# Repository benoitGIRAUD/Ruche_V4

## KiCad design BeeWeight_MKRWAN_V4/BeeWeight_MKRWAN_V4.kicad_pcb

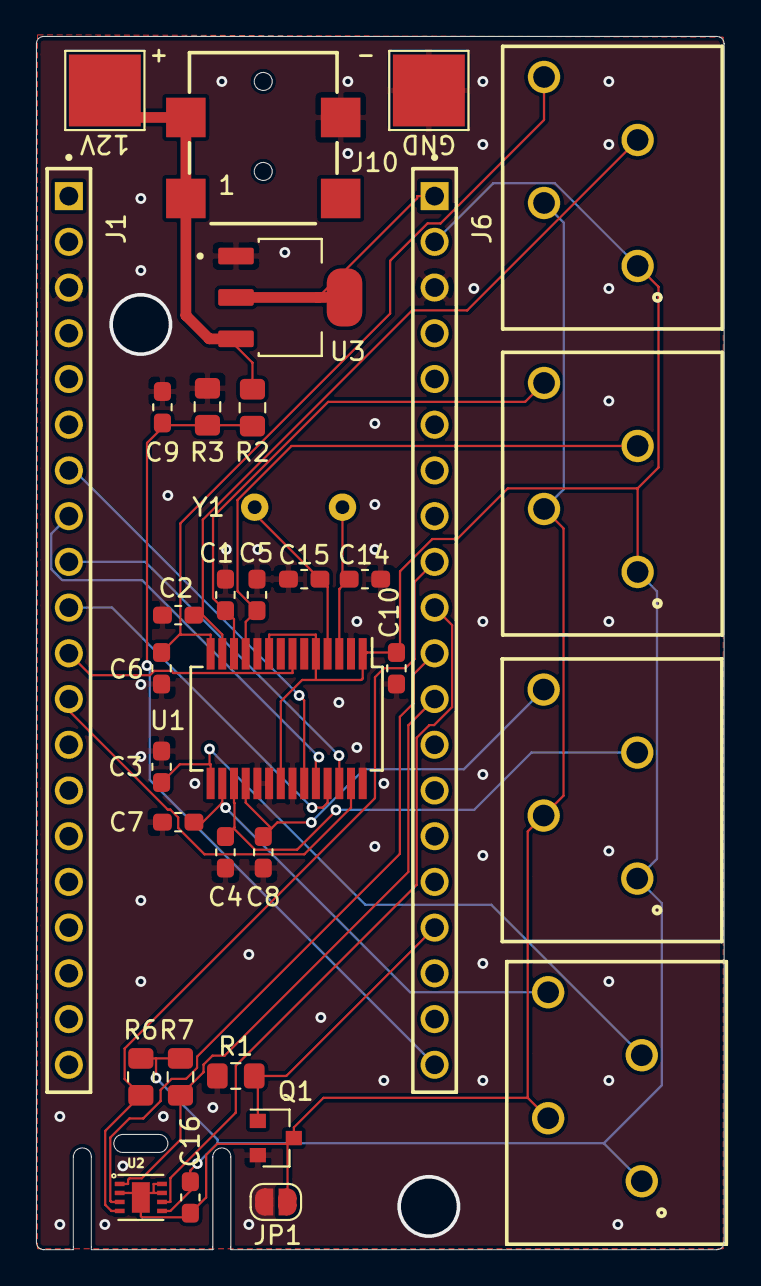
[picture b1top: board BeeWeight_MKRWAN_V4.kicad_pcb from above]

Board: 4 copper layers, 38.2 x 67.4 mm, 33 parts (0 on the bottom side), 27 nets.

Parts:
12V: TestPoint; TestPoint_Pad_4.0x4.0mm
C1, C2, C3, C4, C5, C6, C7, C8: 10nF; C_0603_1608Metric_Pad1.05x0.95mm_HandSolder
C9, C10, C16: 100nF; C_0603_1608Metric_Pad1.05x0.95mm_HandSolder
C14, C15: 18pF; C_0603_1608Metric_Pad1.05x0.95mm_HandSolder
GND: TestPoint; TestPoint_Pad_4.0x4.0mm
J1, J6: SSW-120-01-X-S; SAMTEC_SSW-120-01-X-S
J2, J3, J4, J5: 691412120004B; TermBlock_1x04_P3.50mm Wurth_691412120004B
J10: 694103107102
JP1: SolderJumper_2_Open; SolderJumper-2_P1.3mm_Open_RoundedPad1.0x1.5mm
Q1: IRLML6244; SOT-23
R1: 1M; R_0805_2012Metric_Pad1.15x1.40mm_HandSolder
R2: 560k; R_0805_2012Metric_Pad1.15x1.40mm_HandSolder
R3: 100k; R_0805_2012Metric_Pad1.15x1.40mm_HandSolder
R6, R7: 10K; R_0805_2012Metric_Pad1.15x1.40mm_HandSolder
U1: ADS1241
U2: SHT30-DIS-B; DFN250X250X100-9N
U3: LDL1117S50R; SOT230P700X180-4N
Y1: Crystal; Crystal-4Mhz-TH-Wurth-830027298B

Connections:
/3V3: C10.2, C16.1, J2.1, J3.1, J4.1, J5.1, J6.02, R6.2, R7.2, U1.1, U1.5, U1.9, U1.21, U2.5
/12V: 12V.1, J10.1, J10.A1, R2.2, U3.3
/AIN0: C5.1, J5.3, U1.11
/AIN1: C1.1, J5.4, U1.12
/AIN2: C4.1, J4.3, U1.17
/AIN3: C8.1, J4.4, U1.18
/AIN4: C2.1, J2.3, U1.13
/AIN5: C6.1, J2.4, U1.14
/AIN6: C3.1, J3.3, U1.15
/AIN7: C7.1, J3.4, U1.16
/GND_LowPower: C16.2, J2.2, J3.2, J4.2, J5.2, JP1.1, Q1.3, U2.2, U2.7, U2.8, U2.9
/IO4_VBAT_12V: C9.1, J6.20, R2.1, R3.2
/IO7_CMD_MOS: J6.17, Q1.1, R1.2
/IO17_SDA: J6.12, R7.1, U2.1
/IO18_SCL: J6.09, R6.1, U2.4
/IO19_SHT_ALERT: J6.11, U2.3
/IO21_SHT_RST: J6.10, U2.6
/IO34_CS: J1.07, U1.23
/IO35_MOSI: J1.08, U1.24
/IO36_SCLK: J1.09, U1.26
/IO37_MISO: J1.10, U1.25
/IO38_PDWN: J1.11, U1.7
/IO39_DRDY: J1.12, U1.27
/VDD_5V: J6.01, U3.2, U3.4
GND: C1.2, C2.2, C3.2, C4.2, C5.2, C6.2, C7.2, C8.2, C9.2, C10.1, C14.1, C15.2, GND.1, J1.03, J6.03, J10.2, JP1.2, Q1.2, R1.1, R3.1, U1.2, U1.10, U1.19, U1.20, U1.22, U1.28, U3.1
unnamed: C14.2, U1.3, Y1.1
unnamed: C15.1, U1.4, Y1.2

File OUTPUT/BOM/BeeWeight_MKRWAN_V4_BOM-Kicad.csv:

"Id";"Référence";"Boîtier";"Quantité";"Désignation";"Fournisseur et réf";
1;"U1";"ADS1241";1;"ADS1241";;;
2;"JP1";"SolderJumper-2_P1.3mm_Open_RoundedPad1.0x1.5mm";1;"SolderJumper_2_Open";;;
3;"Y1";"Crystal-4Mhz-TH-Wurth-830027298B";1;"Crystal";;;
4;"J3,J5,J4,J2";"TermBlock_1x04_P3.50mm Wurth_691412120004B";4;"691412120004B";;;
5;"C7,C1,C2,C3,C4,C5,C6,C8";"C_0603_1608Metric_Pad1.05x0.95mm_HandSolder";8;"10nF";;;
6;"C9,C10,C16";"C_0603_1608Metric_Pad1.05x0.95mm_HandSolder";3;"100nF";;;
7;"C14,C15";"C_0603_1608Metric_Pad1.05x0.95mm_HandSolder";2;"18pF";;;
8;"Q1";"SOT-23";1;"IRLML6244";;;
9;"R1";"R_0805_2012Metric_Pad1.15x1.40mm_HandSolder";1;"1M";;;
10;"R2";"R_0805_2012Metric_Pad1.15x1.40mm_HandSolder";1;"560k";;;
11;"R3";"R_0805_2012Metric_Pad1.15x1.40mm_HandSolder";1;"100k";;;
12;"R6,R7";"R_0805_2012Metric_Pad1.15x1.40mm_HandSolder";2;"10K";;;
13;"U2";"DFN250X250X100-9N";1;"SHT30-DIS-B";;;
14;"J10";"694103107102";1;"694103107102";;;
15;"J1";"SAMTEC_SSW-120-01-X-S";1;"SSW-120-01-X-S";;;
16;"J6";"SAMTEC_SSW-120-01-X-S";1;"SSW-120-01-X-S";;;
17;"U3";"SOT230P700X180-4N";1;"LDL1117S50R";;;
18;"GND,12V";"TestPoint_Pad_4.0x4.0mm";2;"TestPoint";;;

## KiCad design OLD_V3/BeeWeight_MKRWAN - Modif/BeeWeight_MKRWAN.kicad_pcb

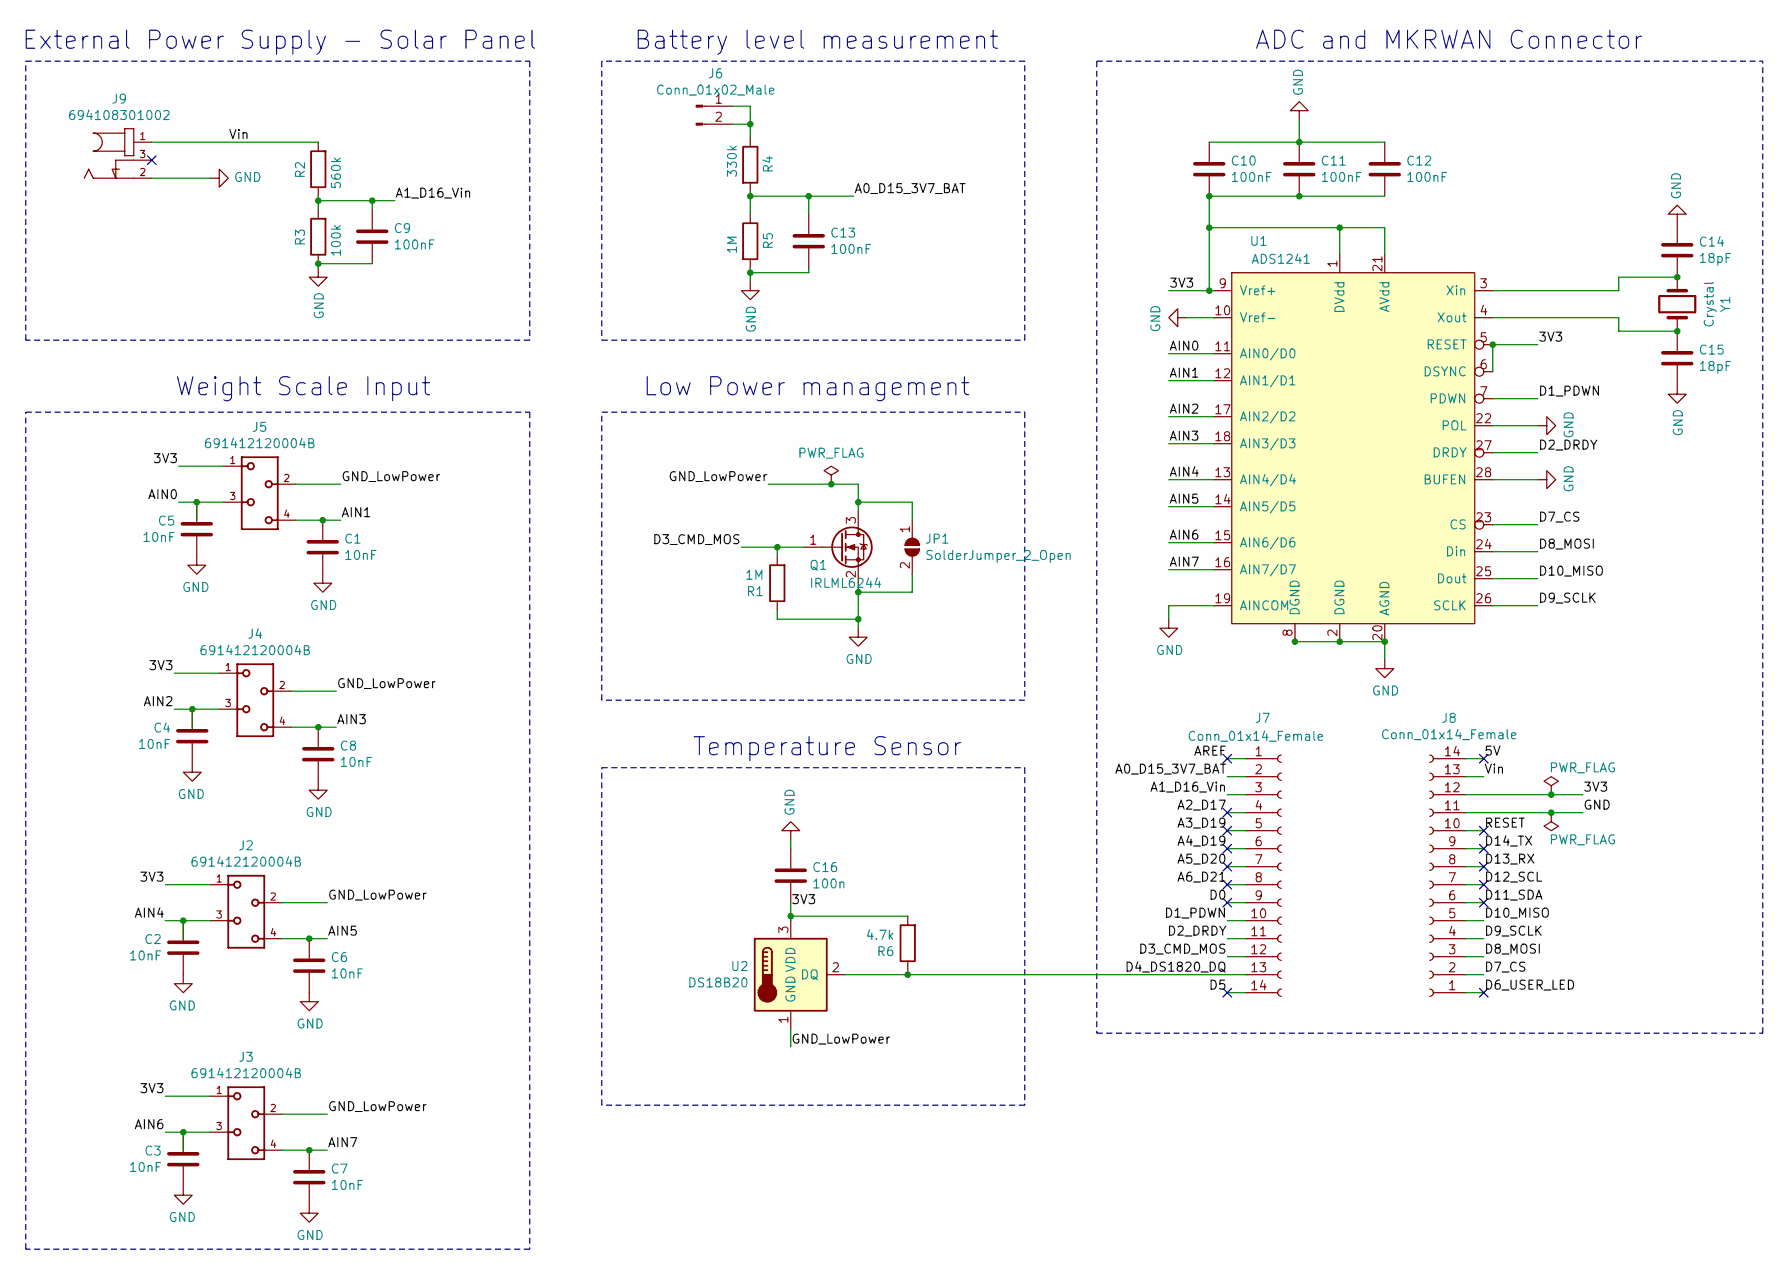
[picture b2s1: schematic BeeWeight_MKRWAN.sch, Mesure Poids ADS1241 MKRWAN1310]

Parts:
C1, C2, C3, C4, C5, C6, C7, C8: 10nF; C_0603_1608Metric_Pad1.05x0.95mm_HandSolder
C9, C10, C11, C12, C13: 100nF; C_0603_1608Metric_Pad1.05x0.95mm_HandSolder
C14, C15: 18pF; C_0603_1608Metric_Pad1.05x0.95mm_HandSolder
C16: 100n; C_0603_1608Metric_Pad1.05x0.95mm_HandSolder
J2, J3, J4, J5: 691412120004B; TermBlock_1x04_P3.50mm Wurth_691412120004B; PART-NUMBER 691412120004B
J6: Conn_01x02_Male; PinHeader_1x02_P2.54mm_Horizontal
J7, J8: Conn_01x14_Female; PinSocket_1x14_P2.54mm_Vertical
J9: 694108301002; Jack_DC_2.1mm Wurth_694108301002; PART-NUMBER 694108301002
JP1: SolderJumper_2_Open; SolderJumper-2_P1.3mm_Open_RoundedPad1.0x1.5mm
Q1: IRLML6244; SOT-23
R1, R5: 1M; R_0805_2012Metric_Pad1.15x1.40mm_HandSolder
R2: 560k; R_0805_2012Metric_Pad1.15x1.40mm_HandSolder
R3: 100k; R_0805_2012Metric_Pad1.15x1.40mm_HandSolder
R4: 330k; R_0805_2012Metric_Pad1.15x1.40mm_HandSolder
R6: 4.7k; R_0805_2012Metric_Pad1.15x1.40mm_HandSolder
U1: ADS1241
U2: DS18B20; TO-92
Y1: Crystal; Crystal-4Mhz-TH-Wurth-830027298B

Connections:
/3V3: C10.2, C11.2, C12.2, C16.2, J2.1, J3.1, J4.1, J5.1, J8.12, R6.2, U1.1 (DVdd), U1.5 (RESET), U1.6 (DSYNC), U1.9 (Vref+), U1.21 (AVdd), U2.3 (VDD)
/5V: J8.14
/A0_D15_3V7_BAT: C13.1, J7.2, R4.2, R5.1
/A1_D16_Vin: C9.1, J7.3, R2.1, R3.2
/A2_D17: J7.4
/A3_D19: J7.5
/A4_D19: J7.6
/A5_D20: J7.7
/A6_D21: J7.8
/AIN0: C5.1, J5.3, U1.11 (AIN0/D0)
/AIN1: C1.1, J5.4, U1.12 (AIN1/D1)
/AIN2: C4.1, J4.3, U1.17 (AIN2/D2)
/AIN3: C8.1, J4.4, U1.18 (AIN3/D3)
/AIN4: C2.1, J2.3, U1.13 (AIN4/D4)
/AIN5: C6.1, J2.4, U1.14 (AIN5/D5)
/AIN6: C3.1, J3.3, U1.15 (AIN6/D6)
/AIN7: C7.1, J3.4, U1.16 (AIN7/D7)
/AREF: J7.1
/D0: J7.9
/D1_PDWN: J7.10, U1.7 (PDWN)
/D2_DRDY: J7.11, U1.27 (DRDY)
/D3_CMD_MOS: J7.12, Q1.1 (G), R1.2
/D4_DS1820_DQ: J7.13, R6.1, U2.2 (DQ)
/D5: J7.14
/D6_USER_LED: J8.1
/D7_CS: J8.2, U1.23 (CS)
/D8_MOSI: J8.3, U1.24 (Din)
/D9_SCLK: J8.4, U1.26 (SCLK)
/D10_MISO: J8.5, U1.25 (Dout)
/D11_SDA: J8.6
/D12_SCL: J8.7
/D13_RX: J8.8
/D14_TX: J8.9
/GND_LowPower: J2.2, J3.2, J4.2, J5.2, JP1.1 (A), Q1.3 (D), U2.1 (GND)
/RESET: J8.10
/Vin: J8.13, J9.1, R2.2
GND: C1.2, C2.2, C3.2, C4.2, C5.2, C6.2, C7.2, C8.2, C9.2, C10.1, C11.1, C12.1, C13.2, C14.1, C15.2, C16.1, J8.11, J9.2, JP1.2 (B), Q1.2 (S), R1.1, R3.1, R5.2, U1.2 (DGND), U1.8 (DGND), U1.10 (Vref-), U1.19 (AINCOM), U1.20 (AGND), U1.22 (POL), U1.28 (BUFEN)
unnamed: C14.2, U1.3 (Xin), Y1.1
unnamed: C15.1, U1.4 (Xout), Y1.2
unnamed: J6.1, J6.2, R4.1

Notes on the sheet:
External Power Supply - Solar Panel
Weight Scale Input
Battery level measurement
Low Power management
Temperature Sensor
ADC and MKRWAN Connector

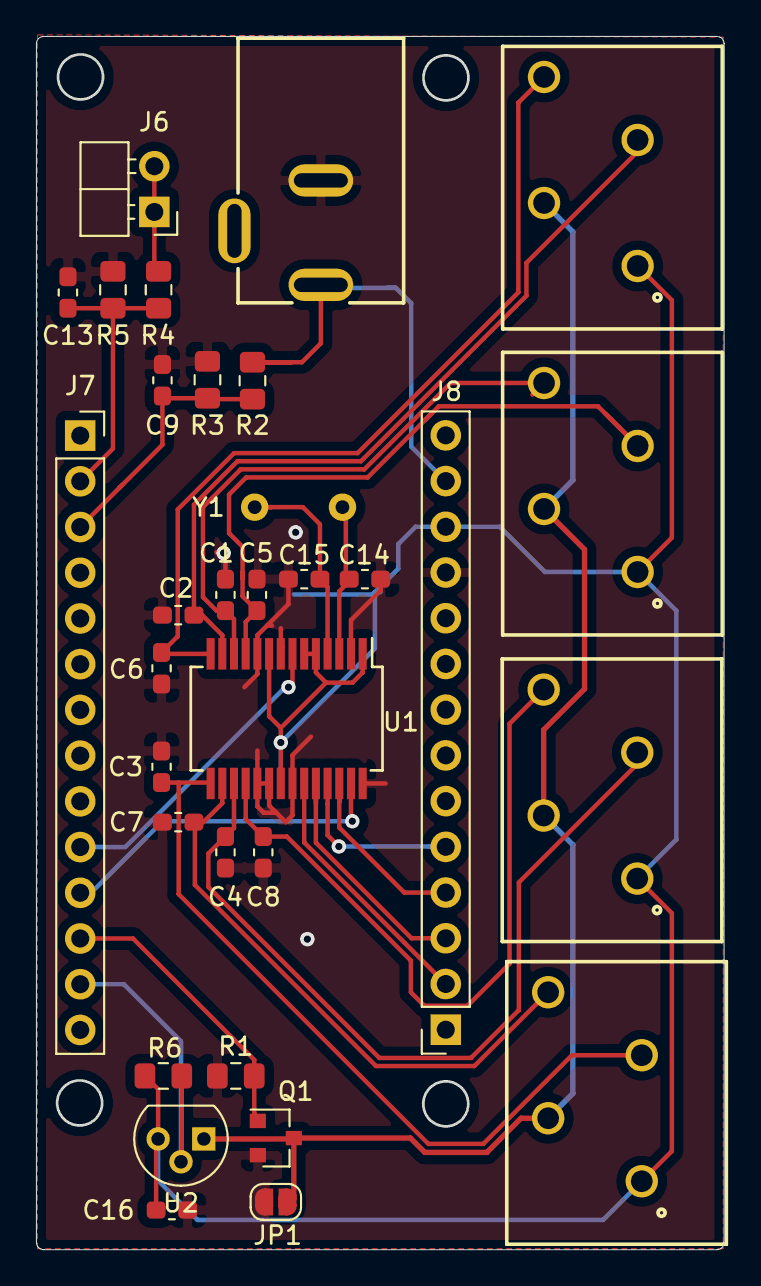
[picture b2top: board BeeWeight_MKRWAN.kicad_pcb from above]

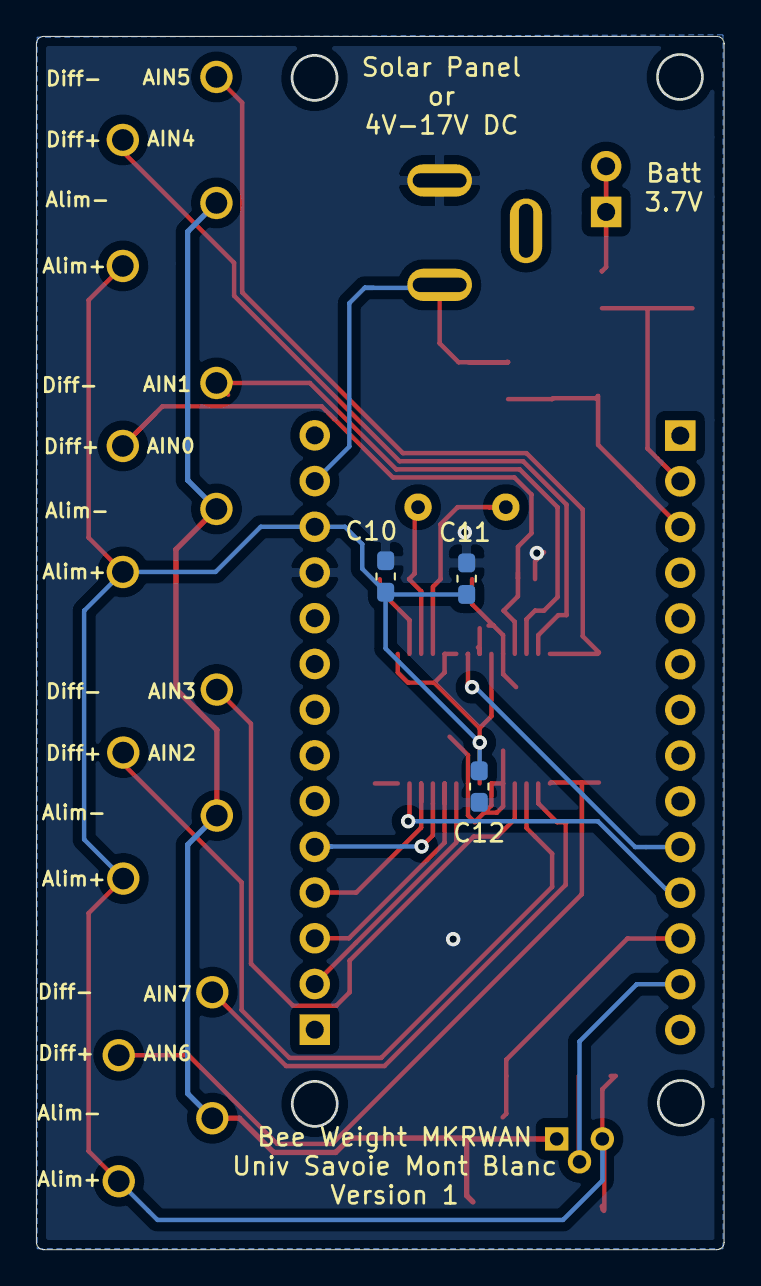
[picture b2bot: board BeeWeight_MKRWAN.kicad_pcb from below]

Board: 2 copper layers, 38.1 x 67.3 mm, 35 parts (3 on the bottom side), 25 nets.

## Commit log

2023-08-28 Recuperation CAO sur NAS + V-Heltec
2023-08-28 ajout new componets and new board in folder
2023-08-28 Lundi soir : en cours de pin mapping
2023-08-29 Mardi soir: pinout routé sur le schematic
2023-08-29 Tout mis au propre (chemin + pistes et positions)
2023-08-29 FINISHED
2023-08-30 Send to JLCPCB
